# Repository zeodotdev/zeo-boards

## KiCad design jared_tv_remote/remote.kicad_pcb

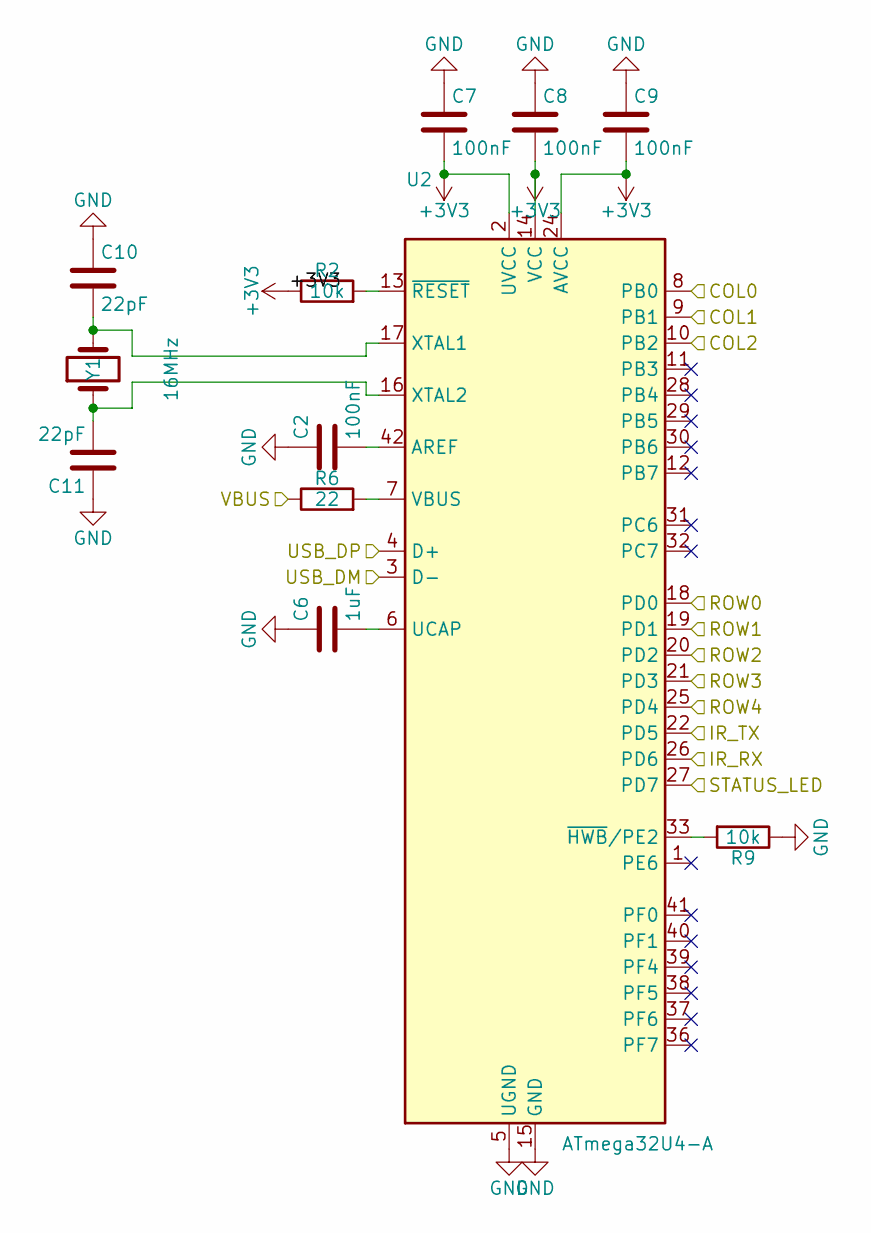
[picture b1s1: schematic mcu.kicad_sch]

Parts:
C2, C7, C8, C9: 100nF; C_0402_1005Metric
C6: 1uF; C_0402_1005Metric
C10, C11: 22pF; C_0402_1005Metric
R2, R9: 10k; R_0402_1005Metric
R6: 22; R_0402_1005Metric
U2: ATmega32U4-A; TQFP-44_10x10mm_P0.8mm
Y1: 16MHz; Crystal_SMD_3215-2Pin_3.2x1.5mm

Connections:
+3V3: C7.2, C8.2, C9.2, R2.1, U2.2 (UVCC), U2.14 (VCC), U2.24 (AVCC), U2.34 (VCC), U2.44 (AVCC); also elsewhere on the board
/COL0: U2.8 (PB0); also elsewhere on the board
/COL1: U2.9 (PB1); also elsewhere on the board
/COL2: U2.10 (PB2); also elsewhere on the board
/IR_RX: U2.26 (PD6); also elsewhere on the board
/IR_TX: U2.22 (PD5); also elsewhere on the board
/ROW0: U2.18 (PD0); also elsewhere on the board
/ROW1: U2.19 (PD1); also elsewhere on the board
/ROW2: U2.20 (PD2); also elsewhere on the board
/ROW3: U2.21 (PD3); also elsewhere on the board
/ROW4: U2.25 (PD4); also elsewhere on the board
/STATUS_LED: U2.27 (PD7); also elsewhere on the board
/USB_DM: U2.3 (D-); also elsewhere on the board
/USB_DP: U2.4 (D+); also elsewhere on the board
/VBUS: R6.1; also elsewhere on the board
unnamed: C2.2, U2.42 (AREF)
unnamed: C6.2, U2.6 (UCAP)
unnamed: R6.2, U2.7 (VBUS)
unnamed: C10.2, U2.17 (XTAL1), Y1.2
unnamed: C11.2, U2.16 (XTAL2), Y1.1
unnamed: R9.2, U2.33 (~HWB/PE2)
unnamed: R2.2, U2.13 (~RESET)

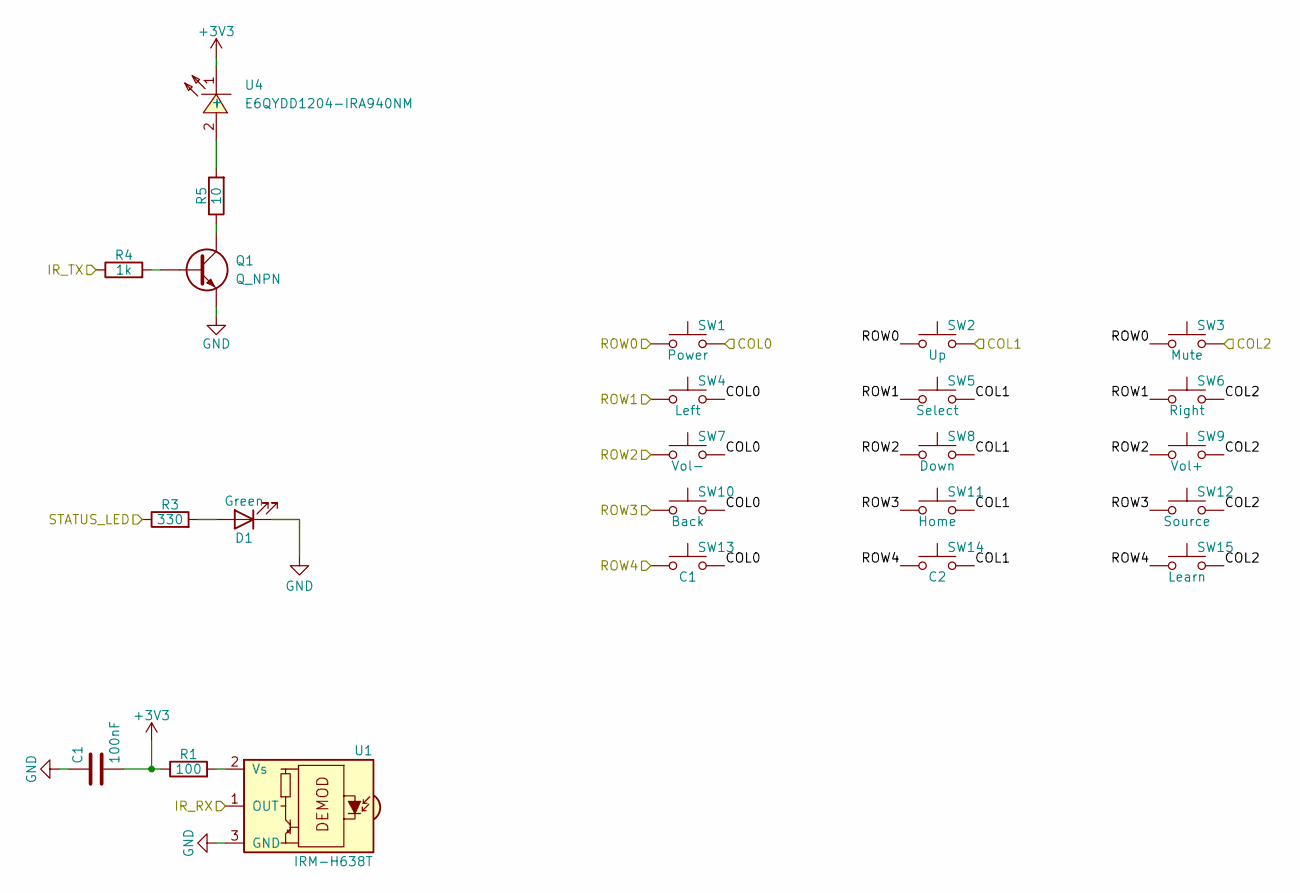
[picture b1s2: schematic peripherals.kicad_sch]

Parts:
C1: 100nF; C_0402_1005Metric
D1: Green; LED_0603_1608Metric
Q1: Q_NPN; SOT-23
R1: 100; R_0402_1005Metric
R3: 330; R_0402_1005Metric
R4: 1k; R_0402_1005Metric
R5: 10; R_0805_2012Metric
SW1: Power; SW_SPST_B3SL-1002P
SW2: Up; SW_SPST_B3SL-1002P
SW3: Mute; SW_SPST_B3SL-1002P
SW4: Left; SW_SPST_B3SL-1002P
SW5: Select; SW_SPST_B3SL-1002P
SW6: Right; SW_SPST_B3SL-1002P
SW7: Vol-; SW_SPST_B3SL-1002P
SW8: Down; SW_SPST_B3SL-1002P
SW9: Vol+; SW_SPST_B3SL-1002P
SW10: Back; SW_SPST_B3SL-1002P
SW11: Home; SW_SPST_B3SL-1002P
SW12: Source; SW_SPST_B3SL-1002P
SW13: C1; SW_SPST_B3SL-1002P
SW14: C2; SW_SPST_B3SL-1002P
SW15: Learn; SW_SPST_B3SL-1002P
U1: IRM-H638T; Everlight_IRM-H6xxT
U4: E6QYDD1204-IRA940NM; LED-SMD_L3.2-W2.1-R-FD; LCSC Part C396649

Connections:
+3V3: C1.2, R1.1, U4.1 (-); also elsewhere on the board
/COL0: SW1.2, SW4.2, SW7.2, SW10.2, SW13.2; also elsewhere on the board
/COL1: SW2.2, SW5.2, SW8.2, SW11.2, SW14.2; also elsewhere on the board
/COL2: SW3.2, SW6.2, SW9.2, SW12.2, SW15.2; also elsewhere on the board
/IR_RX: U1.1 (OUT); also elsewhere on the board
/IR_TX: R4.1; also elsewhere on the board
/ROW0: SW1.1, SW2.1, SW3.1; also elsewhere on the board
/ROW1: SW4.1, SW5.1, SW6.1; also elsewhere on the board
/ROW2: SW7.1, SW8.1, SW9.1; also elsewhere on the board
/ROW3: SW10.1, SW11.1, SW12.1; also elsewhere on the board
/ROW4: SW13.1, SW14.1, SW15.1; also elsewhere on the board
/STATUS_LED: R3.1; also elsewhere on the board
unnamed: D1.2 (A), R3.2
unnamed: Q1.1 (B), R4.2
unnamed: Q1.2 (C), R5.1
unnamed: R1.2, U1.2 (Vs)
unnamed: R5.2, U4.2 (+)

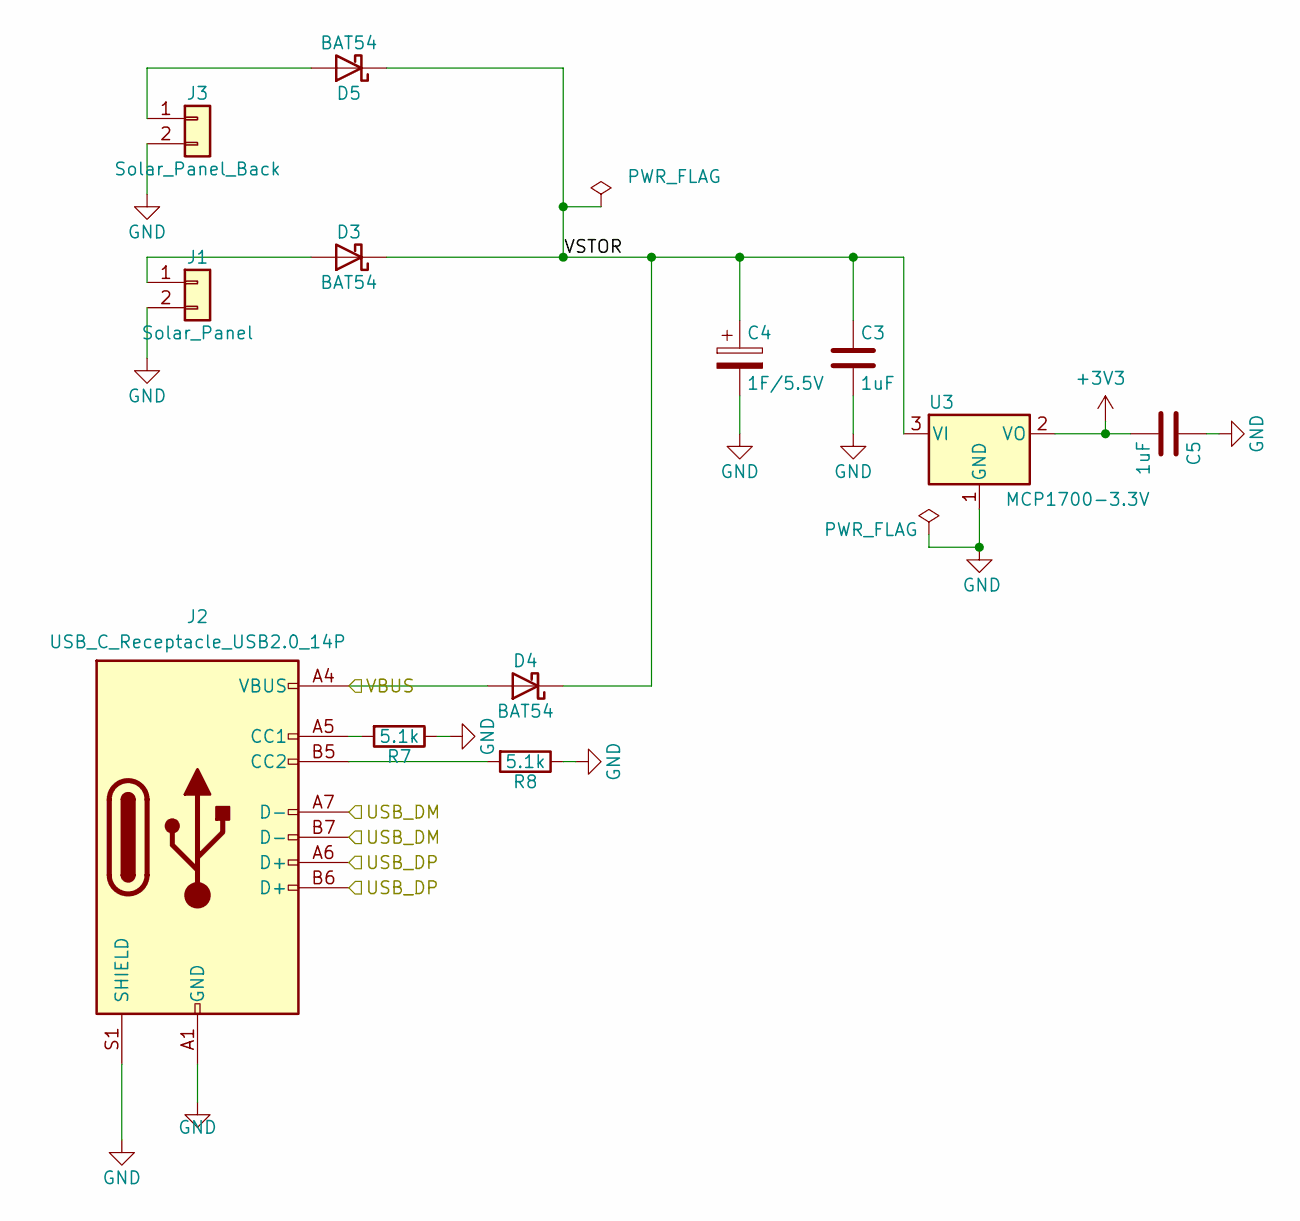
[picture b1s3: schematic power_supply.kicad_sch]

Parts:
C3, C5: 1uF; C_0402_1005Metric
C4: 1F/5.5V; C_1210_3225Metric
D3, D4, D5: BAT54; D_SOD-323
J1: Solar_Panel; SolderWire-0.5sqmm_1x02_P4.6mm_D0.9mm_OD2.1mm
J2: USB_C_Receptacle_USB2.0_14P; USB_C_Receptacle_HRO_TYPE-C-31-M-12
J3: Solar_Panel_Back; SolderWire-0.5sqmm_1x02_P4.6mm_D0.9mm_OD2.1mm
R7, R8: 5.1k; R_0402_1005Metric
U3: MCP1700-3.3V; SOT-23

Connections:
+3V3: C5.2, U3.2 (VO); also elsewhere on the board
/USB_DM: J2.A7 (D-), J2.B7 (D-); also elsewhere on the board
/USB_DP: J2.A6 (D+), J2.B6 (D+); also elsewhere on the board
/VBUS: D4.2 (A), J2.A4 (VBUS), J2.A9 (VBUS), J2.B4 (VBUS), J2.B9 (VBUS); also elsewhere on the board
unnamed: D3.2 (A), J1.1
unnamed: D5.2 (A), J3.1
unnamed: J2.A5 (CC1), R7.2
unnamed: J2.B5 (CC2), R8.2

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
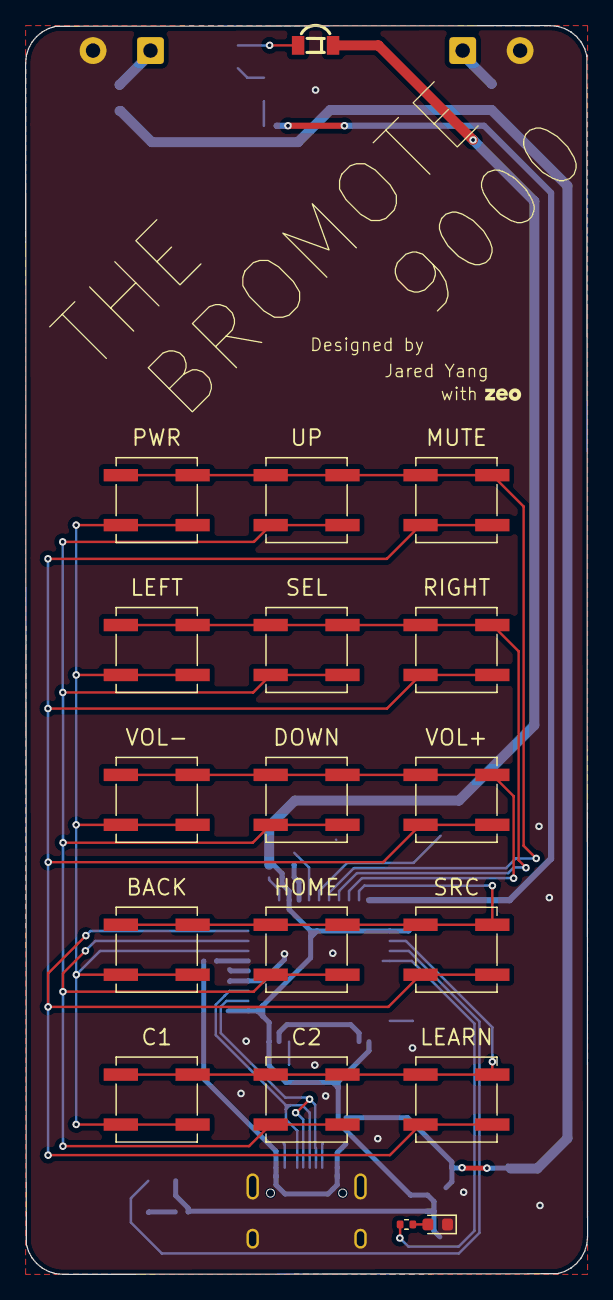
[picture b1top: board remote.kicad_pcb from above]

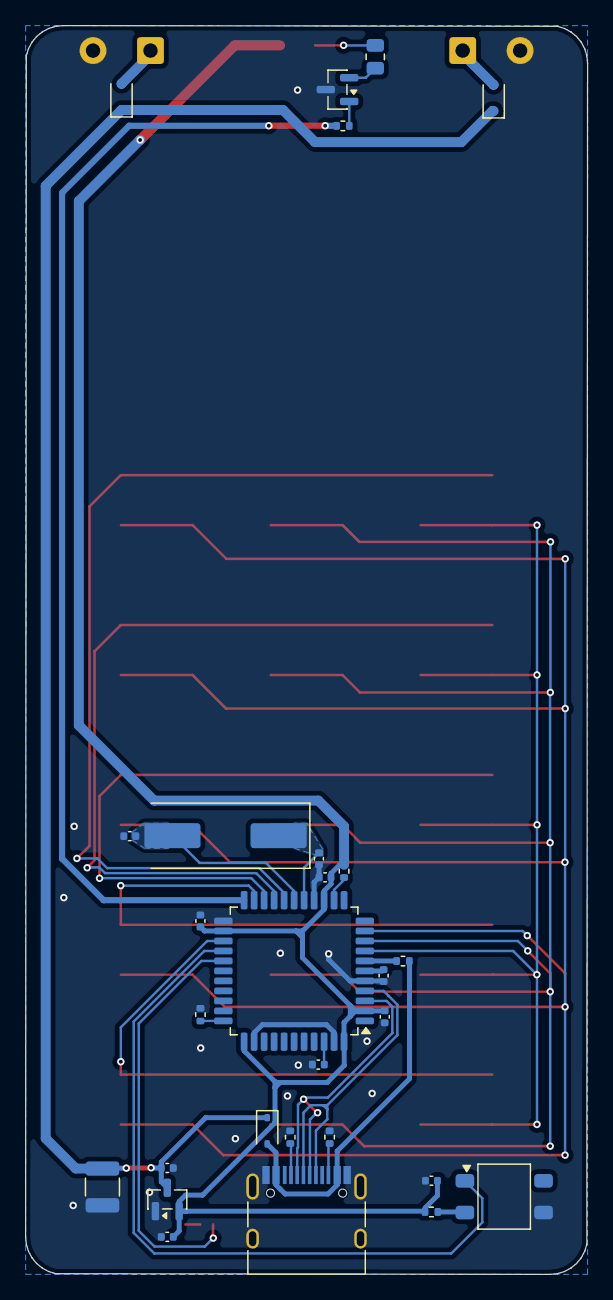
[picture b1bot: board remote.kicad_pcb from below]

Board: 2 copper layers, 45.0 x 100.0 mm, 48 parts (28 on the bottom side), 33 nets.

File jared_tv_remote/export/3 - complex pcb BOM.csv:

Id,Designator,Footprint,Quantity,Comment,Supplier and ref
1,"C1, C2, C7, C8, C9",C_0402_1005Metric,5,100nF,
2,"C3, C5, C6",C_0402_1005Metric,3,1uF,
3,C4,C_1210_3225Metric,1,1F/5.5V,
4,"C10, C11",C_0402_1005Metric,2,22pF,
5,D1,LED_0603_1608Metric,1,Green,
6,D2,LED_D5.0mm,1,IR_940nm,
7,"D3, D4, D5",D_SOD-323,3,BAT54,
8,J1,SolderWire-0.5sqmm_1x02_P4.6mm_D0.9mm_OD2.1mm,1,Solar_Panel,
9,J2,USB_C_Receptacle_HRO_TYPE-C-31-M-12,1,USB_C_Receptacle_USB2.0_14P,
10,J3,SolderWire-0.5sqmm_1x02_P4.6mm_D0.9mm_OD2.1mm,1,Solar_Panel_Back,
11,Q1,SOT-23,1,Q_NPN,
12,R1,R_0402_1005Metric,1,100,
13,"R2, R9",R_0402_1005Metric,2,10k,
14,R3,R_0402_1005Metric,1,330,
15,R4,R_0402_1005Metric,1,1k,
16,R5,R_0805_2012Metric,1,10,
17,R6,R_0402_1005Metric,1,22,
18,"R7, R8",R_0402_1005Metric,2,5.1k,
19,SW1,SW_SPST_B3U-1000P,1,Power,
20,SW2,SW_SPST_B3U-1000P,1,Up,
21,SW3,SW_SPST_B3U-1000P,1,Mute,
22,SW4,SW_SPST_B3U-1000P,1,Left,
23,SW5,SW_SPST_B3U-1000P,1,Select,
24,SW6,SW_SPST_B3U-1000P,1,Right,
25,SW7,SW_SPST_B3U-1000P,1,Vol-,
26,SW8,SW_SPST_B3U-1000P,1,Down,
27,SW9,SW_SPST_B3U-1000P,1,Vol+,
28,SW10,SW_SPST_B3U-1000P,1,Back,
29,SW11,SW_SPST_B3U-1000P,1,Home,
30,SW12,SW_SPST_B3U-1000P,1,Source,
31,SW13,SW_SPST_B3U-1000P,1,C1,
32,SW14,SW_SPST_B3U-1000P,1,C2,
33,SW15,SW_SPST_B3U-1000P,1,Learn,
34,U1,Everlight_IRM-H6xxT,1,IRM-H638T,
35,U2,TQFP-44_10x10mm_P0.8mm,1,ATmega32U4-A,
36,U3,SOT-23,1,MCP1700-3.3V,
37,Y1,Crystal_SMD_3215-2Pin_3.2x1.5mm,1,16MHz,
